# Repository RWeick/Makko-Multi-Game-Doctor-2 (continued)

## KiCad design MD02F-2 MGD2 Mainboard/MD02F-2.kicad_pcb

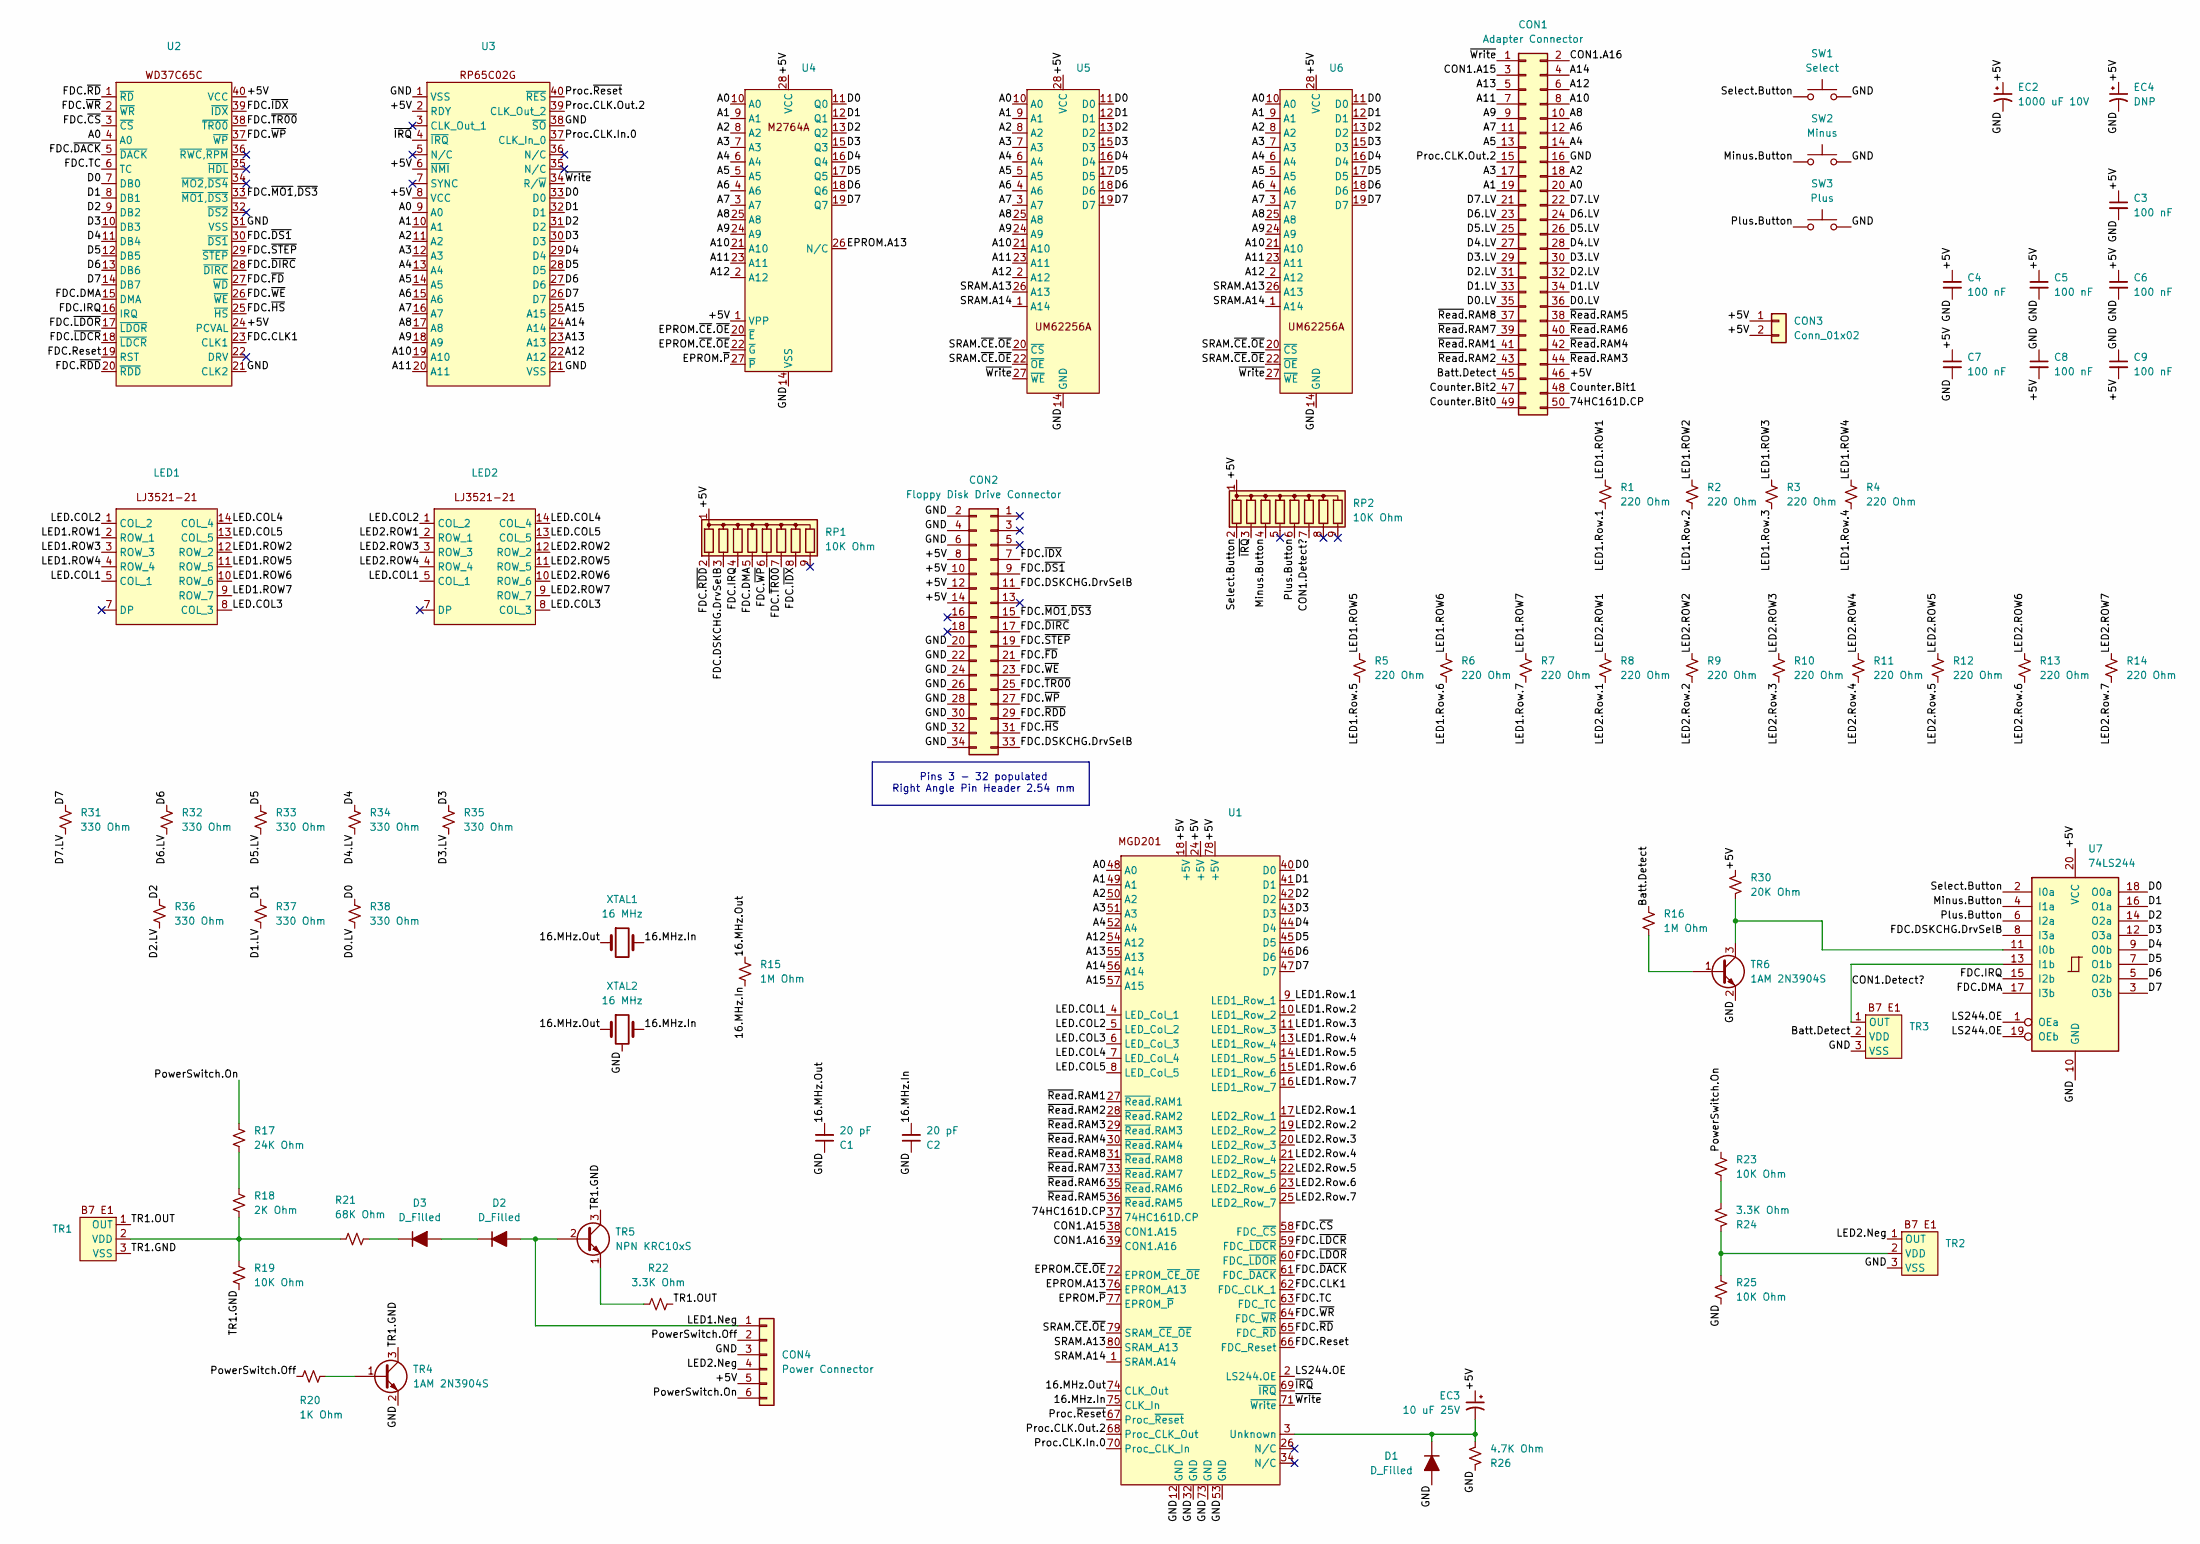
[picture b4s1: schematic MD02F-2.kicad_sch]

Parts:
C1, C2: 20 pF; C_1206_3216Metric
C3, C4, C5, C6, C7, C8, C9: 100 nF; C_1206_3216Metric
CON1: Adapter Connector; J050 Connector
CON2: Floppy Disk Drive Connector; PinHeader_2x17_P2.54mm_Horizontal
CON3: Conn_01x02; PinHeader_1x02_P2.54mm_Vertical
CON4: Power Connector; PinHeader_1x06_P2.54mm_Vertical
D1, D2, D3: D_Filled; D_1206_3216Metric
EC2: 1000 uF 10V; CP_Radial_D8.0mm_P3.50mm
EC3: 10 uF 25V; CP_Radial_D5.0mm_P2.50mm
EC4: DNP; C_1210_3225Metric_Pad1.33x2.70mm_HandSolder
LED1, LED2: DIP-14_W7.62mm
R1, R2, R3, R4, R5, R6, R7, R8, R9, R10, R11, R12, R13, R14: 220 Ohm; R_0805_2012Metric
R15, R16: 1M Ohm; R_0805_2012Metric
R17: 24K Ohm; R_0805_2012Metric
R18: 2K Ohm; R_0805_2012Metric
R19, R23, R25: 10K Ohm; R_0805_2012Metric
R20: 1K Ohm; R_0805_2012Metric
R21: 68K Ohm; R_0805_2012Metric
R22, R24: 3.3K Ohm; R_0805_2012Metric
R26: 4.7K Ohm; R_0805_2012Metric
R30: 20K Ohm; R_0805_2012Metric
R31, R32, R33, R34, R35, R36, R37, R38: 330 Ohm; R_0805_2012Metric
RP1, RP2: 10K Ohm; R_Array_SIP9
SW1: Select; Button
SW2: Minus; Button
SW3: Plus; Button
TR1, TR2, TR3: SOT-89-3
TR4, TR6: 1AM 2N3904S; SOT-23
TR5: NPN KRC10xS; SOT-23
U1: MGD201 QFP-80
U2, U3: DIP-40_W15.24mm
U4, U5: DIP-28_W15.24mm
U6: SOIC-28W_7.5x18.7mm_P1.27mm
U7: 74LS244; DIP-20_W7.62mm
XTAL1: 16 MHz; Crystal_AT310_D3.0mm_L10.0mm_Horizontal
XTAL2: 16 MHz; Crystal_HC18-U_Horizontal_1EP_style1

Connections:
/16.MHz.In: C2.2, R15.2, U1.75 (CLK_In), XTAL1.2, XTAL2.2
/16.MHz.Out: C1.2, R15.1, U1.74 (CLK_Out), XTAL1.1, XTAL2.1
/74HC161D.CP: CON1.50, U1.37 (74HC161D.CP)
/+5V: C3.1, C4.1, C5.1, C6.1, C7.1, C8.2, C9.2, CON1.46, CON2.8, CON2.10, CON2.12, CON2.14, CON3.1, CON3.2, CON4.5, EC2.1, EC3.1, EC4.1, R30.2, RP1.1 (common), RP2.1 (common), U1.18 (+5V), U1.24 (+5V), U1.78 (+5V), U2.24 (PCVAL), U2.40 (VCC), U3.2 (RDY), U3.6 (~NMI), U3.8 (VCC), U4.1 (VPP), U4.28 (VCC), U5.28 (VCC), U6.28 (VCC), U7.20 (VCC)
/A0: CON1.20, U1.48 (A0), U2.4 (A0), U3.9 (A0), U4.10 (A0), U5.10 (A0), U6.10 (A0)
/A1: CON1.19, U1.49 (A1), U3.10 (A1), U4.9 (A1), U5.9 (A1), U6.9 (A1)
/A2: CON1.18, U1.50 (A2), U3.11 (A2), U4.8 (A2), U5.8 (A2), U6.8 (A2)
/A3: CON1.17, U1.51 (A3), U3.12 (A3), U4.7 (A3), U5.7 (A3), U6.7 (A3)
/A4: CON1.14, U1.52 (A4), U3.13 (A4), U4.6 (A4), U5.6 (A4), U6.6 (A4)
/A5: CON1.13, U3.14 (A5), U4.5 (A5), U5.5 (A5), U6.5 (A5)
/A6: CON1.12, U3.15 (A6), U4.4 (A6), U5.4 (A6), U6.4 (A6)
/A7: CON1.11, U3.16 (A7), U4.3 (A7), U5.3 (A7), U6.3 (A7)
/A8: CON1.10, U3.17 (A8), U4.25 (A8), U5.25 (A8), U6.25 (A8)
/A9: CON1.9, U3.18 (A9), U4.24 (A9), U5.24 (A9), U6.24 (A9)
/A10: CON1.8, U3.19 (A10), U4.21 (A10), U5.21 (A10), U6.21 (A10)
/A11: CON1.7, U3.20 (A11), U4.23 (A11), U5.23 (A11), U6.23 (A11)
/A12: CON1.6, U1.54 (A12), U3.22 (A12), U4.2 (A12), U5.2 (A12), U6.2 (A12)
/A13: CON1.5, U1.55 (A13), U3.23 (A13)
/A14: CON1.4, U1.56 (A14), U3.24 (A14)
/A15: U1.57 (A15), U3.25 (A15)
/Batt.Detect: CON1.45, R16.1, TR3.2 (VDD)
/CON1.A15: CON1.3, U1.38 (CON1.A15)
/CON1.A16: CON1.2, U1.39 (CON1.A16)
/CON1.Detect?: RP2.7 (R6), TR3.1 (OUT), U7.13 (I1b)
/Counter.Bit0: CON1.49
/Counter.Bit1: CON1.48
/Counter.Bit2: CON1.47
/D0: R38.1, U1.40 (D0), U2.7 (DB0), U3.33 (D0), U4.11 (Q0), U5.11 (D0), U6.11 (D0), U7.18 (O0a)
/D0.LV: CON1.35, CON1.36, R38.2
/D1: R37.1, U1.41 (D1), U2.8 (DB1), U3.32 (D1), U4.12 (Q1), U5.12 (D1), U6.12 (D1), U7.16 (O1a)
/D1.LV: CON1.33, CON1.34, R37.2
/D2: R36.1, U1.42 (D2), U2.9 (DB2), U3.31 (D2), U4.13 (Q2), U5.13 (D2), U6.13 (D2), U7.14 (O2a)
/D2.LV: CON1.31, CON1.32, R36.2
/D3: R35.1, U1.43 (D3), U2.10 (DB3), U3.30 (D3), U4.15 (Q3), U5.15 (D3), U6.15 (D3), U7.12 (O3a)
/D3.LV: CON1.29, CON1.30, R35.2
/D4: R34.1, U1.44 (D4), U2.11 (DB4), U3.29 (D4), U4.16 (Q4), U5.16 (D4), U6.16 (D4), U7.9 (O0b)
/D4.LV: CON1.27, CON1.28, R34.2
/D5: R33.1, U1.45 (D5), U2.12 (DB5), U3.28 (D5), U4.17 (Q5), U5.17 (D5), U6.17 (D5), U7.7 (O1b)
/D5.LV: CON1.25, CON1.26, R33.2
/D6: R32.1, U1.46 (D6), U2.13 (DB6), U3.27 (D6), U4.18 (Q6), U5.18 (D6), U6.18 (D6), U7.5 (O2b)
/D6.LV: CON1.23, CON1.24, R32.2
/D7: R31.1, U1.47 (D7), U2.14 (DB7), U3.26 (D7), U4.19 (Q7), U5.19 (D7), U6.19 (D7), U7.3 (O3b)
/D7.LV: CON1.21, CON1.22, R31.2
/EPROM.A13: U1.76 (EPROM_A13), U4.26 (N/C)
/EPROM.~CE.~OE: U1.72 (EPROM_~CE_~OE), U4.20 (~E), U4.22 (~G)
/EPROM.~P: U1.77 (EPROM_~P), U4.27 (~P)
/FDC.CLK1: U1.62 (FDC_CLK_1), U2.23 (CLK1)
/FDC.DMA: RP1.5 (R4), U2.15 (DMA), U7.17 (I3b)
/FDC.DSKCHG.DrvSelB: CON2.11, CON2.33, RP1.3 (R2), U7.8 (I3a)
/FDC.IRQ: RP1.4 (R3), U2.16 (IRQ), U7.15 (I2b)
/FDC.Reset: U1.66 (FDC_Reset), U2.19 (RST)
/FDC.TC: U1.63 (FDC_TC), U2.6 (TC)
/FDC.~CS: U1.58 (FDC_~CS), U2.3 (~CS)
/FDC.~DACK: U1.61 (FDC_~DACK), U2.5 (~DACK)
/FDC.~DIRC: CON2.17, U2.28 (~DIRC)
/FDC.~DS1: CON2.9, U2.30 (~DS1)
/FDC.~FD: CON2.21, U2.27 (~WD)
/FDC.~HS: CON2.31, U2.25 (~HS)
/FDC.~IDX: CON2.7, RP1.8 (R7), U2.39 (~IDX)
/FDC.~LDCR: U1.59 (FDC_~LDCR), U2.18 (~LDCR)
/FDC.~LDOR: U1.60 (FDC_~LDOR), U2.17 (~LDOR)
/FDC.~MO1,~DS3: CON2.15, U2.33 (~MO1,~DS3)
/FDC.~RDD: CON2.29, RP1.2 (R1), U2.20 (~RDD)
/FDC.~RD: U1.65 (FDC_~RD), U2.1 (~RD)
/FDC.~STEP: CON2.19, U2.29 (~STEP)
/FDC.~TR00: CON2.25, RP1.7 (R6), U2.38 (~TR00)
/FDC.~WE: CON2.23, U2.26 (~WE)
/FDC.~WP: CON2.27, RP1.6 (R5), U2.37 (~WP)
/FDC.~WR: U1.64 (FDC_~WR), U2.2 (~WR)
/GND: C1.1, C2.1, C3.2, C4.2, C5.2, C6.2, C7.2, C8.1, C9.1, CON1.16, CON2.2, CON2.4, CON2.6, CON2.20, CON2.22, CON2.24, CON2.26, CON2.28, CON2.30, CON2.32, CON2.34, CON4.3, D1.2 (A), EC2.2, EC4.2, R25.2, R26.1, SW1.2, SW2.2, SW3.2, TR2.3 (VSS), TR3.3 (VSS), TR4.2 (E), TR6.2 (E), U1.12 (GND), U1.32 (GND), U1.53 (GND), U1.73 (GND), U2.21 (CLK2), U2.31 (VSS), U3.1 (VSS), U3.21 (VSS), U3.38 (~SO), U4.14 (VSS), U5.14 (GND), U6.14 (GND), U7.10 (GND), XTAL2.3
/LED1.Neg: CON4.1, D2.2 (A), TR5.2 (B)
/LED1.ROW1: LED1.2 (ROW_1), R1.1
/LED1.ROW2: LED1.12 (ROW_2), R2.1
/LED1.ROW3: LED1.3 (ROW_3), R3.1
/LED1.ROW4: LED1.4 (ROW_4), R4.1
/LED1.ROW5: LED1.11 (ROW_5), R5.1
/LED1.ROW6: LED1.10 (ROW_6), R6.1
/LED1.ROW7: LED1.9 (ROW_7), R7.1
/LED1.Row.1: R1.2, U1.9 (LED1_Row_1)
/LED1.Row.2: R2.2, U1.10 (LED1_Row_2)
/LED1.Row.3: R3.2, U1.11 (LED1_Row_3)
/LED1.Row.4: R4.2, U1.13 (LED1_Row_4)
/LED1.Row.5: R5.2, U1.14 (LED1_Row_5)
/LED1.Row.6: R6.2, U1.15 (LED1_Row_6)
/LED1.Row.7: R7.2, U1.16 (LED1_Row_7)
/LED2.Neg: CON4.4, TR2.1 (OUT)
/LED2.ROW1: LED2.2 (ROW_1), R8.1
/LED2.ROW2: LED2.12 (ROW_2), R9.1
/LED2.ROW3: LED2.3 (ROW_3), R10.1
/LED2.ROW4: LED2.4 (ROW_4), R11.1
/LED2.ROW5: LED2.11 (ROW_5), R12.1
/LED2.ROW6: LED2.10 (ROW_6), R13.1
/LED2.ROW7: LED2.9 (ROW_7), R14.1
/LED2.Row.1: R8.2, U1.17 (LED2_Row_1)
/LED2.Row.2: R9.2, U1.19 (LED2_Row_2)
/LED2.Row.3: R10.2, U1.20 (LED2_Row_3)
/LED2.Row.4: R11.2, U1.21 (LED2_Row_4)
/LED2.Row.5: R12.2, U1.22 (LED2_Row_5)
/LED2.Row.6: R13.2, U1.23 (LED2_Row_6)
/LED2.Row.7: R14.2, U1.25 (LED2_Row_7)
/LED.COL1: LED1.5 (COL_1), LED2.5 (COL_1), U1.4 (LED_Col_1)
/LED.COL2: LED1.1 (COL_2), LED2.1 (COL_2), U1.5 (LED_Col_2)
/LED.COL3: LED1.8 (COL_3), LED2.8 (COL_3), U1.6 (LED_Col_3)
/LED.COL4: LED1.14 (COL_4), LED2.14 (COL_4), U1.7 (LED_Col_4)
/LED.COL5: LED1.13 (COL_5), LED2.13 (COL_5), U1.8 (LED_Col_5)
/LS244.OE: U1.2 (LS244.OE), U7.1 (OEa), U7.19 (OEb)
/Minus.Button: RP2.4 (R3), SW2.1, U7.4 (I1a)
/Plus.Button: RP2.6 (R5), SW3.1, U7.6 (I2a)
/PowerSwitch.Off: CON4.2, R20.2
/PowerSwitch.On: CON4.6, R17.1, R23.1
/Proc.CLK.In.0: U1.70 (Proc_CLK_In), U3.37 (CLK_In_0)
/Proc.CLK.Out.2: CON1.15, U1.68 (Proc_CLK_Out), U3.39 (CLK_Out_2)
/Proc.~Reset: U1.67 (Proc_~Reset), U3.40 (~RES)
/SRAM.A13: U1.80 (SRAM_A13), U5.26 (A13), U6.26 (A13)
/SRAM.A14: U1.1 (SRAM.A14), U5.1 (A14), U6.1 (A14)
/SRAM.~CE.~OE: U1.79 (SRAM_~CE_~OE), U5.20 (~CS), U5.22 (~OE), U6.20 (~CS), U6.22 (~OE)
/Select.Button: RP2.2 (R1), SW1.1, U7.2 (I0a)
/TR1.GND: R19.2, TR1.3 (VSS), TR4.3 (C), TR5.3 (C)
/TR1.OUT: R22.2, TR1.1 (OUT)
/~IRQ: RP2.3 (R2), U1.69 (~IRQ), U3.4 (~IRQ)
/~Read.RAM1: CON1.41, U1.27 (~Read.RAM1)
/~Read.RAM2: CON1.43, U1.28 (~Read.RAM2)
/~Read.RAM3: CON1.44, U1.29 (~Read.RAM3)
/~Read.RAM4: CON1.42, U1.30 (~Read.RAM4)
/~Read.RAM5: CON1.38, U1.36 (~Read.RAM5)
/~Read.RAM6: CON1.40, U1.35 (~Read.RAM6)
/~Read.RAM7: CON1.39, U1.33 (~Read.RAM7)
/~Read.RAM8: CON1.37, U1.31 (~Read.RAM8)
/~Write: CON1.1, U1.71 (~Write), U3.34 (R/~W), U5.27 (~WE), U6.27 (~WE)
unnamed: D1.1 (K), EC3.2, R26.2, U1.3 (Unknown)
unnamed: D2.1 (K), D3.2 (A)
unnamed: D3.1 (K), R21.1
unnamed: R17.2, R18.1
unnamed: R23.2, R24.2
unnamed: R18.2, R19.1, R21.2, TR1.2 (VDD)
unnamed: R24.1, R25.1, TR2.2 (VDD)
unnamed: R20.1, TR4.1 (B)
unnamed: R22.1, TR5.1 (E)
unnamed: R16.2, TR6.1 (B)
unnamed: R30.1, TR6.3 (C), U7.11 (I0b)

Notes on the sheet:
Pins 3 - 32 populated Right Angle Pin Header 2.54 mm

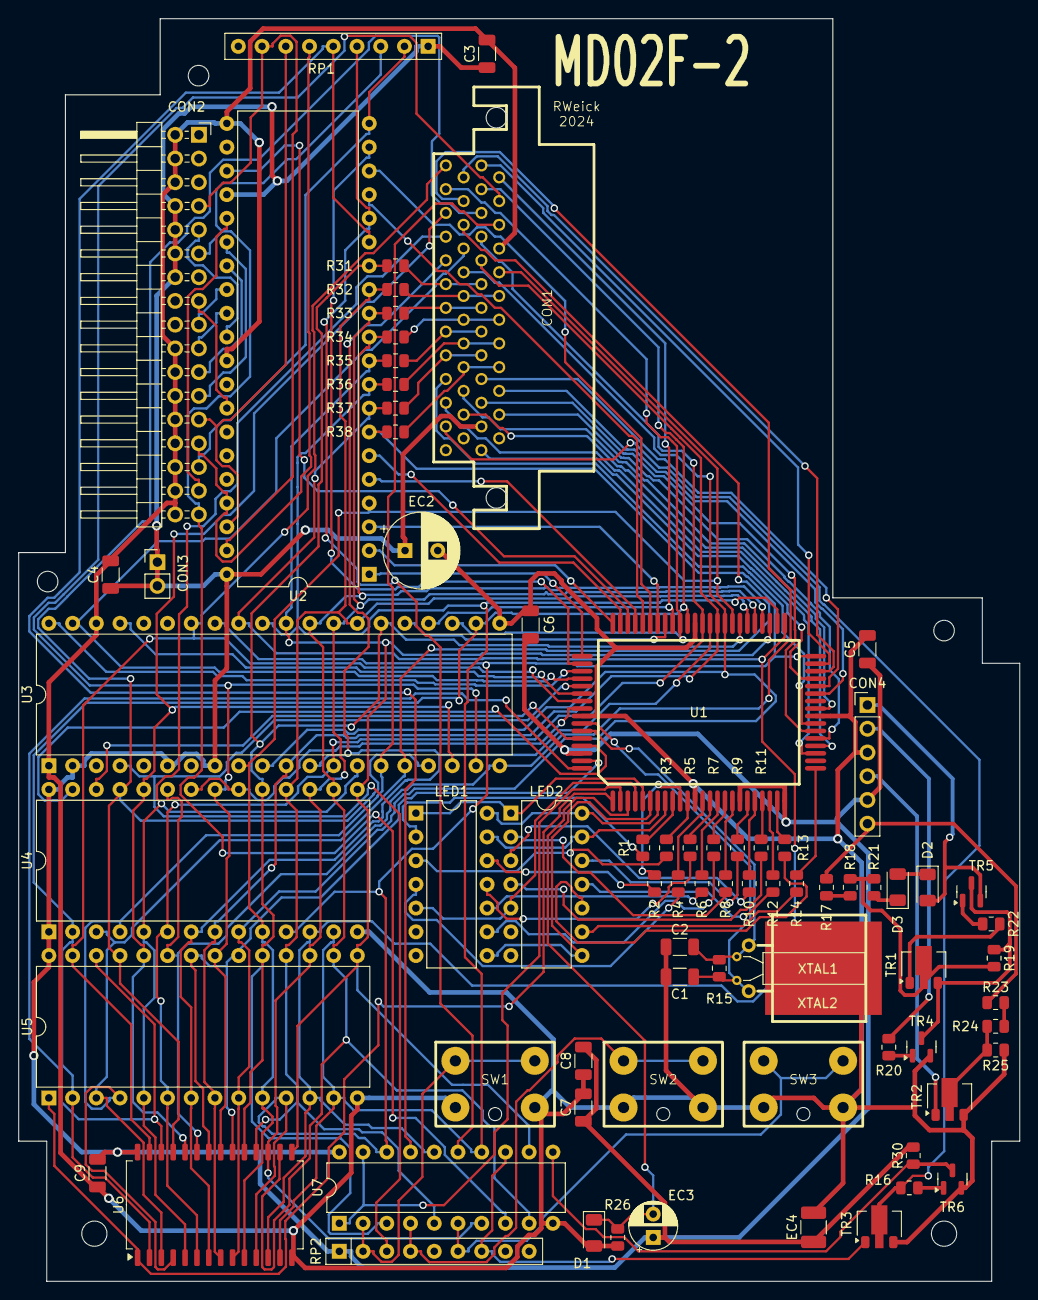
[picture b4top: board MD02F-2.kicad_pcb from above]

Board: 2 copper layers, 107.1 x 135.2 mm, 76 parts (0 on the bottom side), 137 nets.

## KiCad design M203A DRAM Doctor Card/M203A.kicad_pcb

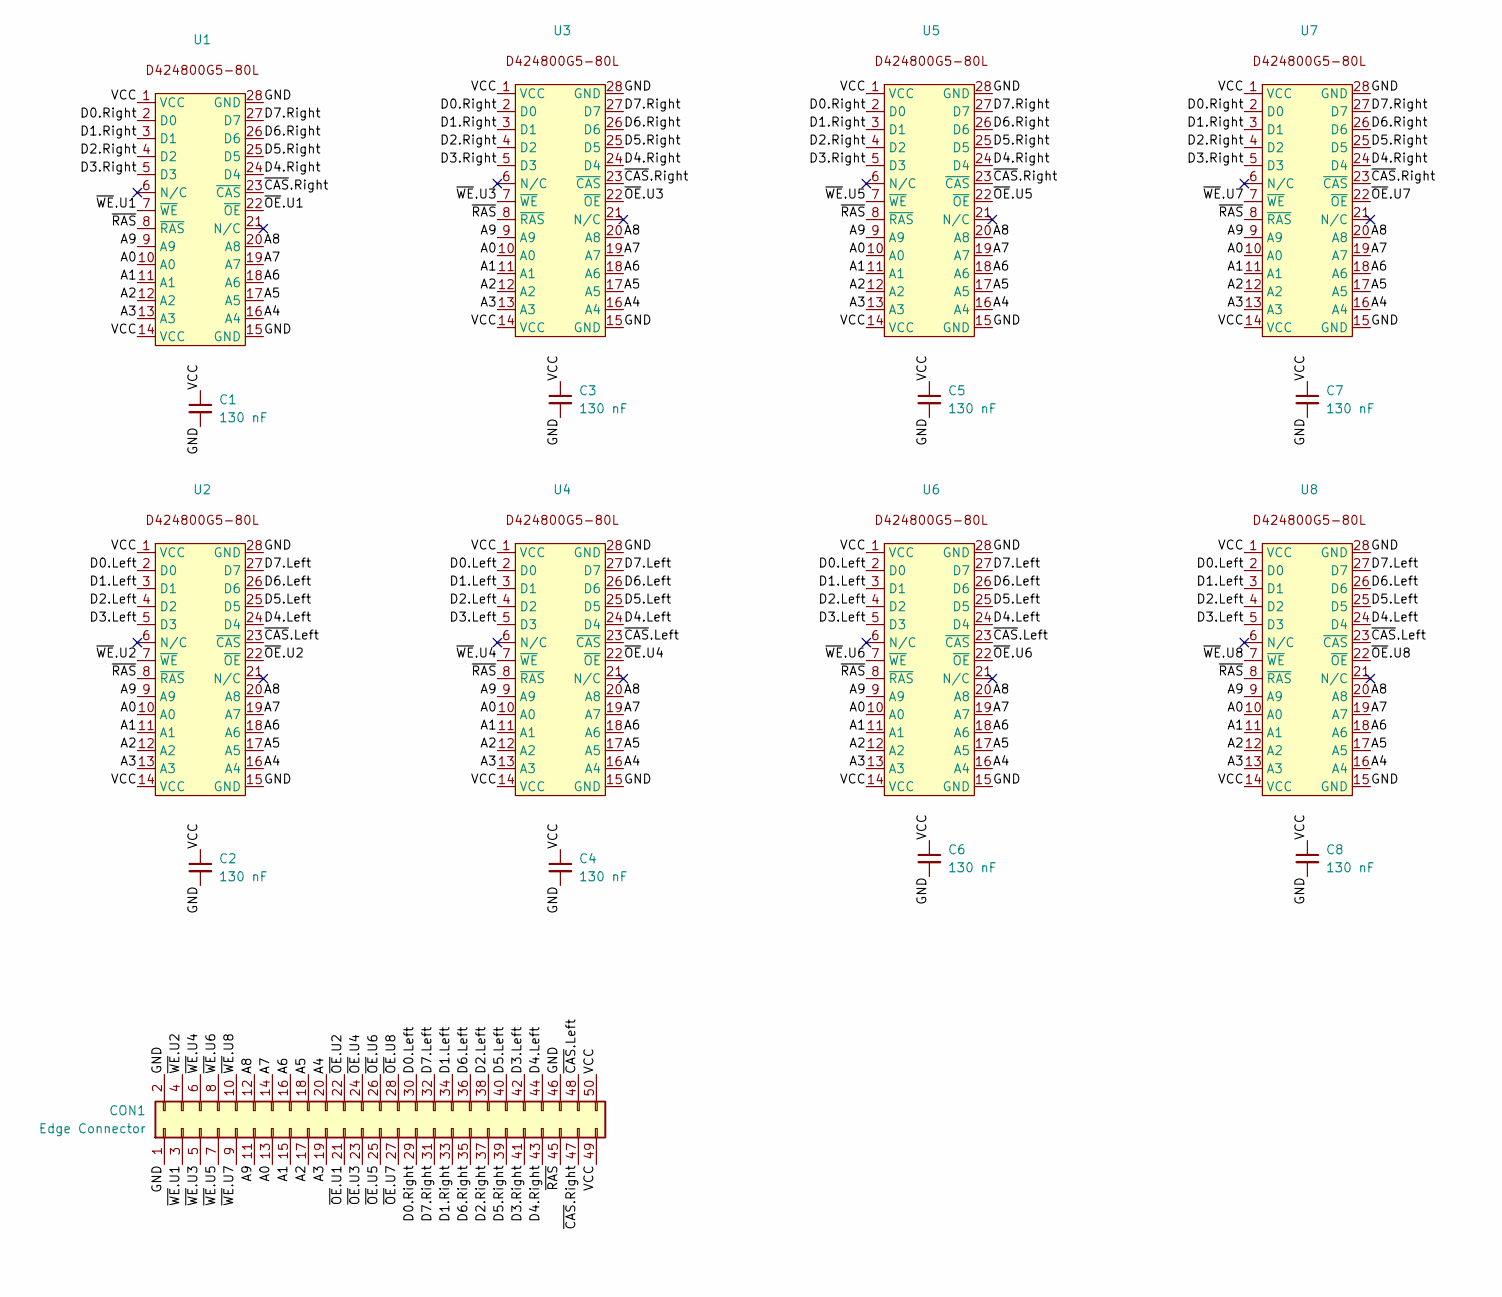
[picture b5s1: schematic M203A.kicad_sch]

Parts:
C1, C2, C3, C4, C5, C6, C7, C8: 130 nF; Capacitor
CON1: Edge Connector
U1, U2, U3, U4, U5, U6, U7, U8: SOIC-28

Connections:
/A0: CON1.13, U1.10 (A0), U2.10 (A0), U3.10 (A0), U4.10 (A0), U5.10 (A0), U6.10 (A0), U7.10 (A0), U8.10 (A0)
/A1: CON1.15, U1.11 (A1), U2.11 (A1), U3.11 (A1), U4.11 (A1), U5.11 (A1), U6.11 (A1), U7.11 (A1), U8.11 (A1)
/A2: CON1.17, U1.12 (A2), U2.12 (A2), U3.12 (A2), U4.12 (A2), U5.12 (A2), U6.12 (A2), U7.12 (A2), U8.12 (A2)
/A3: CON1.19, U1.13 (A3), U2.13 (A3), U3.13 (A3), U4.13 (A3), U5.13 (A3), U6.13 (A3), U7.13 (A3), U8.13 (A3)
/A4: CON1.20, U1.16 (A4), U2.16 (A4), U3.16 (A4), U4.16 (A4), U5.16 (A4), U6.16 (A4), U7.16 (A4), U8.16 (A4)
/A5: CON1.18, U1.17 (A5), U2.17 (A5), U3.17 (A5), U4.17 (A5), U5.17 (A5), U6.17 (A5), U7.17 (A5), U8.17 (A5)
/A6: CON1.16, U1.18 (A6), U2.18 (A6), U3.18 (A6), U4.18 (A6), U5.18 (A6), U6.18 (A6), U7.18 (A6), U8.18 (A6)
/A7: CON1.14, U1.19 (A7), U2.19 (A7), U3.19 (A7), U4.19 (A7), U5.19 (A7), U6.19 (A7), U7.19 (A7), U8.19 (A7)
/A8: CON1.12, U1.20 (A8), U2.20 (A8), U3.20 (A8), U4.20 (A8), U5.20 (A8), U6.20 (A8), U7.20 (A8), U8.20 (A8)
/A9: CON1.11, U1.9 (A9), U2.9 (A9), U3.9 (A9), U4.9 (A9), U5.9 (A9), U6.9 (A9), U7.9 (A9), U8.9 (A9)
/D0.Left: CON1.30, U2.2 (D0), U4.2 (D0), U6.2 (D0), U8.2 (D0)
/D0.Right: CON1.29, U1.2 (D0), U3.2 (D0), U5.2 (D0), U7.2 (D0)
/D1.Left: CON1.34, U2.3 (D1), U4.3 (D1), U6.3 (D1), U8.3 (D1)
/D1.Right: CON1.33, U1.3 (D1), U3.3 (D1), U5.3 (D1), U7.3 (D1)
/D2.Left: CON1.38, U2.4 (D2), U4.4 (D2), U6.4 (D2), U8.4 (D2)
/D2.Right: CON1.37, U1.4 (D2), U3.4 (D2), U5.4 (D2), U7.4 (D2)
/D3.Left: CON1.42, U2.5 (D3), U4.5 (D3), U6.5 (D3), U8.5 (D3)
/D3.Right: CON1.41, U1.5 (D3), U3.5 (D3), U5.5 (D3), U7.5 (D3)
/D4.Left: CON1.44, U2.24 (D4), U4.24 (D4), U6.24 (D4), U8.24 (D4)
/D4.Right: CON1.43, U1.24 (D4), U3.24 (D4), U5.24 (D4), U7.24 (D4)
/D5.Left: CON1.40, U2.25 (D5), U4.25 (D5), U6.25 (D5), U8.25 (D5)
/D5.Right: CON1.39, U1.25 (D5), U3.25 (D5), U5.25 (D5), U7.25 (D5)
/D6.Left: CON1.36, U2.26 (D6), U4.26 (D6), U6.26 (D6), U8.26 (D6)
/D6.Right: CON1.35, U1.26 (D6), U3.26 (D6), U5.26 (D6), U7.26 (D6)
/D7.Left: CON1.32, U2.27 (D7), U4.27 (D7), U6.27 (D7), U8.27 (D7)
/D7.Right: CON1.31, U1.27 (D7), U3.27 (D7), U5.27 (D7), U7.27 (D7)
/GND: C1.2, C2.2, C3.2, C4.2, C5.2, C6.2, C7.2, C8.2, CON1.1, CON1.2, CON1.46, U1.15 (GND), U1.28 (GND), U2.15 (GND), U2.28 (GND), U3.15 (GND), U3.28 (GND), U4.15 (GND), U4.28 (GND), U5.15 (GND), U5.28 (GND), U6.15 (GND), U6.28 (GND), U7.15 (GND), U7.28 (GND), U8.15 (GND), U8.28 (GND)
/VCC: C1.1, C2.1, C3.1, C4.1, C5.1, C6.1, C7.1, C8.1, CON1.49, CON1.50, U1.1 (VCC), U1.14 (VCC), U2.1 (VCC), U2.14 (VCC), U3.1 (VCC), U3.14 (VCC), U4.1 (VCC), U4.14 (VCC), U5.1 (VCC), U5.14 (VCC), U6.1 (VCC), U6.14 (VCC), U7.1 (VCC), U7.14 (VCC), U8.1 (VCC), U8.14 (VCC)
/~CAS.Left: CON1.48, U2.23 (~CAS), U4.23 (~CAS), U6.23 (~CAS), U8.23 (~CAS)
/~CAS.Right: CON1.47, U1.23 (~CAS), U3.23 (~CAS), U5.23 (~CAS), U7.23 (~CAS)
/~OE.U1: CON1.21, U1.22 (~OE)
/~OE.U2: CON1.22, U2.22 (~OE)
/~OE.U3: CON1.23, U3.22 (~OE)
/~OE.U4: CON1.24, U4.22 (~OE)
/~OE.U5: CON1.25, U5.22 (~OE)
/~OE.U6: CON1.26, U6.22 (~OE)
/~OE.U7: CON1.27, U7.22 (~OE)
/~OE.U8: CON1.28, U8.22 (~OE)
/~RAS: CON1.45, U1.8 (~RAS), U2.8 (~RAS), U3.8 (~RAS), U4.8 (~RAS), U5.8 (~RAS), U6.8 (~RAS), U7.8 (~RAS), U8.8 (~RAS)
/~WE.U1: CON1.3, U1.7 (~WE)
/~WE.U2: CON1.4, U2.7 (~WE)
/~WE.U3: CON1.5, U3.7 (~WE)
/~WE.U4: CON1.6, U4.7 (~WE)
/~WE.U5: CON1.7, U5.7 (~WE)
/~WE.U6: CON1.8, U6.7 (~WE)
/~WE.U7: CON1.9, U7.7 (~WE)
/~WE.U8: CON1.10, U8.7 (~WE)

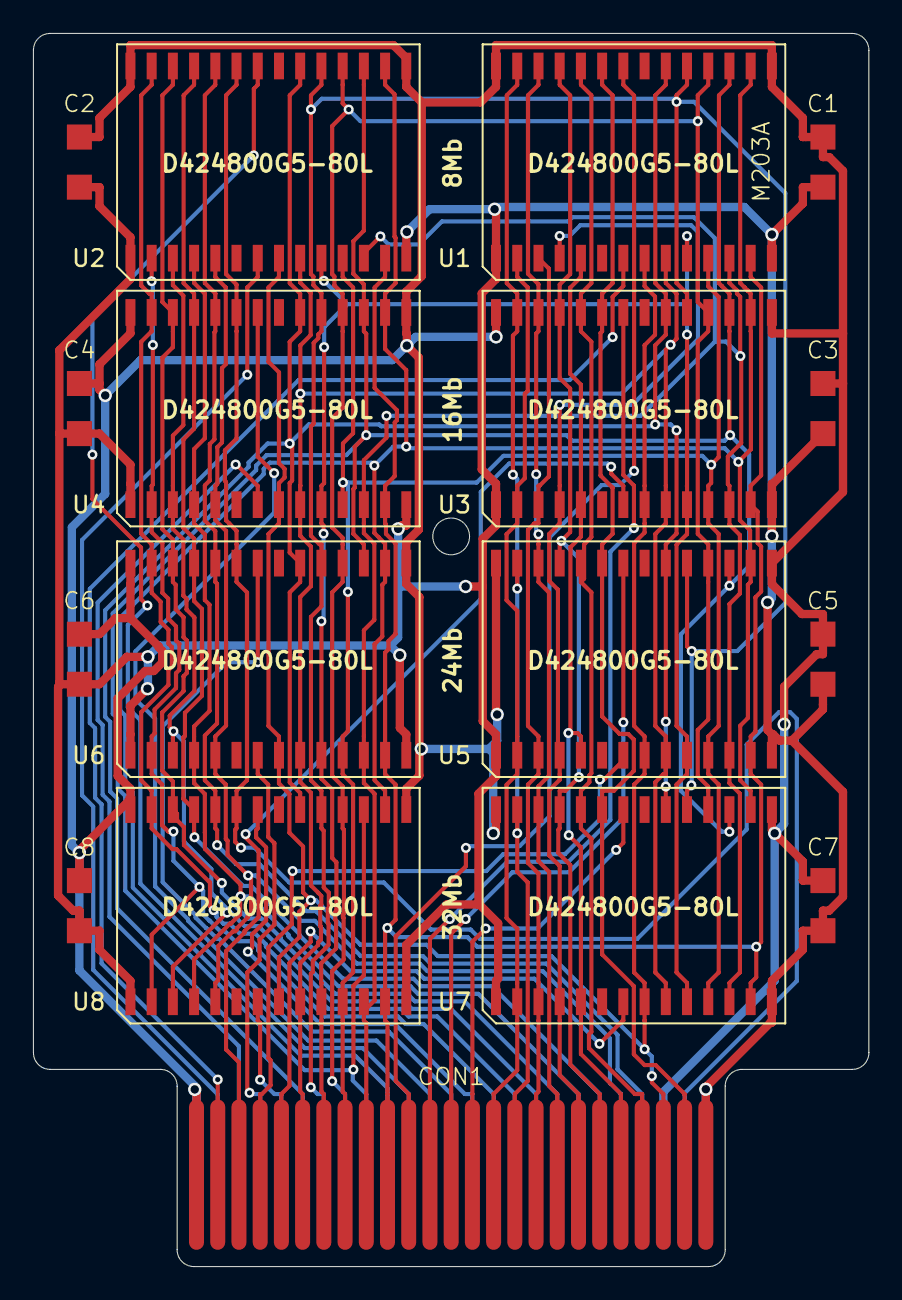
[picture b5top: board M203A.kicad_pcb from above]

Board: 2 copper layers, 50.0 x 73.8 mm, 17 parts (0 on the bottom side), 47 nets.

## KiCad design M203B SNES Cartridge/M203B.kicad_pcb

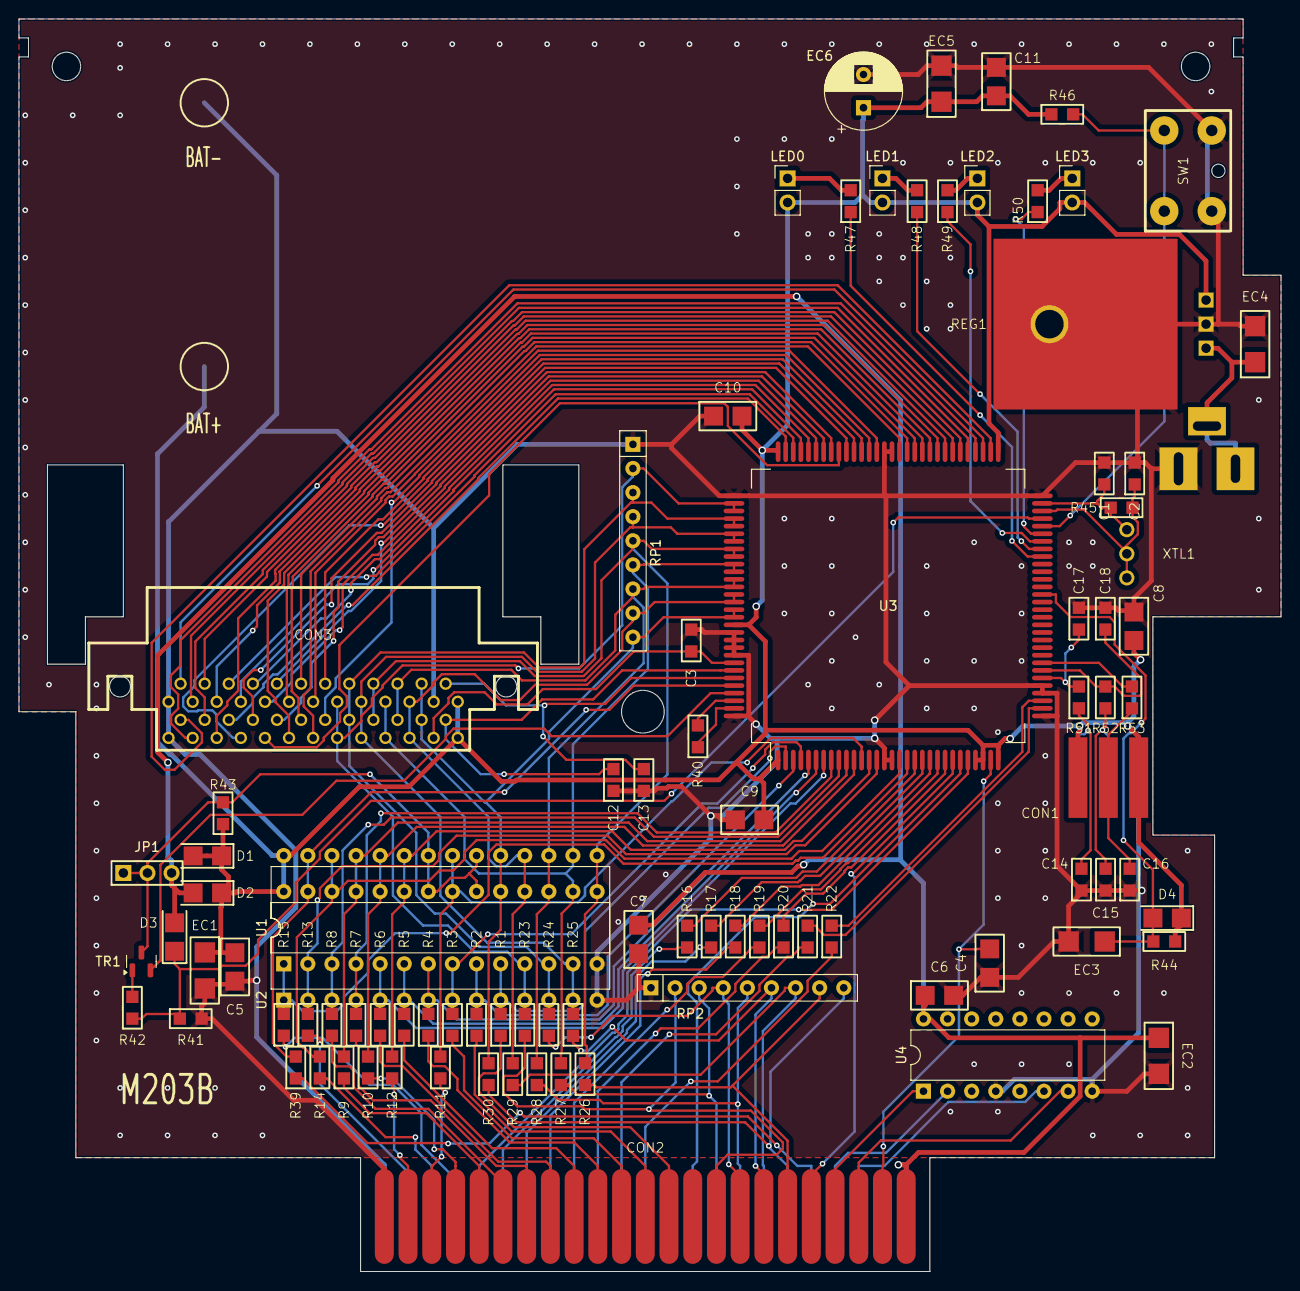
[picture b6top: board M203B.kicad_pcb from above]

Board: 2 copper layers, 133.0 x 132.0 mm, 93 parts (0 on the bottom side), 127 nets.

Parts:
BT1: Battery_Cell; Battery
C1, C2: 20 pF; Resistor
C3, C12, C13, C16: DNP; Resistor
C4: DNP; Capacitor
C5, C6, C7, C8, C9, C10, C11: 200 nF; Capacitor
C14, C15: 190 pF; Resistor
C17, C18: 100 pF; Resistor
CON1: RJ12 Board Connector; RJ-12 Pads
CON2: Edge Connector
CON3: RAM Board Slot; J050 Connector
D1, D2: DNP; Diode
D3: 330 Ohm Resistor; Diode
D4: Populated; Diode
EC1, EC5: DNP; ECap
EC2, EC3: 106 6.3V; ECap
EC4: 200 nF SMD; ECap
EC6: 220 uF 16V; CP_Radial_D8.0mm_P3.50mm
J1: Barrel_Jack_Switch; DC Jack
JP1: DNP; PinHeader_1x03_P2.54mm_Vertical
LED0, LED1, LED2, LED3: LED; PinHeader_1x02_P2.54mm_Vertical
R1, R2, R3, R4, R5, R6, R7, R8, R9, R10, R11, R12, R13, R14, R15, R16, R17, R18, R19, R20, R21, R22, R23, R24, R25, R26, R27, R28, R29, R30, R39, R40, R41, R47, R48, R49, R50, R51, R52, R53: 330 Ohm; Resistor
R42: 1K Ohm; Resistor
R43: Oh Boy; Resistor
R44, R46: 10K Ohm; Resistor
R45: DNP; Resistor
REG1: VREG
RP1, RP2: DNP; R_Array_SIP9
SW1: SW_Push; Button
TR1: 2N3904S; SOT-23
U1: DIP-28_W7.62mm
U2: DIP-28_W15.24mm
U3: MGD203
U4: DIP-16_W7.62mm
XTL1: 16 MHz; Crystal

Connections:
/9V.In: EC4.1, J1.2, REG1.1 (VIN)
/+5V: BT1.1 (+), C5.2, C8.1, C9.2, C10.2, C11.1, CON1.1, CON1.3, CON3.49, CON3.50, D1.1 (K), D1.2 (A), D2.1 (K), D4.1 (K), EC1.1, EC5.1, EC6.1, LED0.2 (A), LED1.2 (A), LED2.2 (A), LED3.2 (A), R43.1, R44.2, R46.1, REG1.3 (VOUT), U1.28 (VCC), U2.28 (VCC), U3.1 (+5V), U3.27 (+5V), U3.28 (+5V), U3.30 (+5V), U3.61 (+5V), U3.90 (+5V), U3.108 (+5V)
/A0: R1.2, U1.10 (A0), U2.10 (A0), U3.2 (A0)
/A0.RAM: CON3.13, U3.80 (A0.RAM)
/A0.Sys: CON2.17 (A0), R1.1
/A1: R2.2, U1.9 (A1), U2.9 (A1), U3.3 (A1)
/A1.RAM: CON3.15, U3.81 (A1.RAM)
/A1.Sys: CON2.16 (A1), R2.1
/A2: R3.2, U1.8 (A2), U2.8 (A2), U3.4 (A2)
/A2.RAM: CON3.17, U3.82 (A2.RAM)
/A2.Sys: CON2.15 (A2), R3.1
/A3: R4.2, U1.7 (A3), U2.7 (A3), U3.5 (A3)
/A3.RAM: CON3.19, U3.83 (A3.RAM)
/A3.Sys: CON2.14 (A3), R4.1
/A4: R5.2, U1.6 (A4), U2.6 (A4), U3.6 (A4)
/A4.RAM: CON3.20, U3.84 (A4.RAM)
/A4.Sys: CON2.13 (A4), R5.1
/A5: R6.2, U1.5 (A5), U2.5 (A5), U3.7 (A5)
/A5.RAM: CON3.18, U3.85 (A5.RAM)
/A5.Sys: CON2.12 (A5), R6.1
/A6: R7.2, U1.4 (A6), U2.4 (A6), U3.8 (A6)
/A6.RAM: CON3.16, U3.86 (A6.RAM)
/A6.Sys: CON2.11 (A6), R7.1
/A7: R8.2, U1.3 (A7), U2.3 (A7), U3.9 (A7)
/A7.RAM: CON3.14, U3.87 (A7.RAM)
/A7.Sys: CON2.10 (A7), R8.1
/A8: R9.2, U1.25 (A8), U2.25 (A8), U3.10 (A8)
/A8.RAM: CON3.12, U3.88 (A8.RAM)
/A8.Sys: CON2.9 (A8), R9.1
/A9: R10.2, U1.24 (A9), U2.24 (A9), U3.11 (A9)
/A9.RAM: CON3.11, U3.89 (A9.RAM)
/A9.Sys: CON2.8 (A9), R10.1
/A10: R11.2, U1.21 (A10), U2.21 (A10), U3.12 (A10)
/A10.Sys: CON2.7 (A10), R11.1
/A11: R12.2, U1.23 (A11), U2.23 (A11), U3.13 (A11)
/A11.Sys: CON2.6 (A11), R12.1
/A12: R13.2, U1.2 (A12), U2.2 (A12), U3.14 (A12)
/A12.Sys: CON2.37 (A12), R13.1
/A13: R14.2, U1.26 (A13), U2.26 (A13), U3.17 (A13)
/A13.Sys: CON2.38 (A13), R14.1
/A14: R15.2, U1.1 (A14), U2.1 (A14), U3.18 (A14)
/A14.Sys: CON2.39 (A14), R15.1
/A15.Sys: CON2.40 (A15), U3.26 (A15.Sys)
/BA0: R16.2, U3.19 (BA0)
/BA0.Sys: CON2.41 (BA0), R16.1
/BA1: R17.2, U3.20 (BA1)
/BA1.Sys: CON2.42 (BA1), R17.1
/BA2: R18.2, U3.21 (BA2)
/BA2.Sys: CON2.43 (BA2), R18.1
/BA3: R19.2, U3.22 (BA3)
/BA3.Sys: CON2.44 (BA3), R19.1
/BA4: R20.2, U3.23 (BA4)
/BA4.Sys: CON2.45 (BA4), R20.1
/BA5: R21.2, U3.32 (BA5)
/BA5.Sys: CON2.46 (BA5), R21.1
/BA6: R22.2, U3.33 (BA6)
/BA6.Sys: CON2.47 (BA6), R22.1
/Button: R46.2, SW1.1, U3.56 (Button)
/CIC.In.P6: CON2.56 (CIC_In_P6), U4.6
/CIC.In.P7: CON2.25 (CIC_In_P7), U4.7
/CIC.Out.P1.Sys: CON2.24 (CIC_Out_P1), U4.1
/CIC.Out.P2.Sys: CON2.55 (CIC_Out_P2), U4.2
/CLK.In: C1.1, R45.1, U3.59 (CLK_In), XTL1.1
/CLK.Out: C2.1, R45.2, U3.58 (CLK_Out), XTL1.2, XTL1.3
/D0: CON3.29, CON3.30, R23.2, RP1.2 (R1), U1.11 (D0), U2.11 (D0), U3.92 (D0), U3.93 (D0)
/D0.Sys: CON2.19 (D0), R23.1, RP2.2 (R1)
/D1: CON3.31, CON3.32, R24.2, RP1.3 (R2), U1.12 (D1), U2.12 (D1), U3.94 (D1), U3.95 (D1)
/D1.Sys: CON2.20 (D1), R24.1, RP2.4 (R3)
/D2: CON3.33, CON3.34, R25.2, RP1.4 (R3), U1.13 (D2), U2.13 (D2), U3.96 (D2), U3.97 (D2)
/D2.Sys: CON2.21 (D2), R25.1, RP2.6 (R5)
/D3: CON3.35, CON3.36, R26.2, RP1.5 (R4), U1.15 (D3), U2.15 (D3), U3.98 (D3), U3.99 (D3)
/D3.Sys: CON2.22 (D3), R26.1, RP2.8 (R7)
/D4: CON3.37, CON3.38, R27.2, RP1.6 (R5), U1.16 (D4), U2.16 (D4), U3.100 (D4), U3.101 (D4)
/D4.Sys: CON2.50 (D4), R27.1, RP2.3 (R2)
/D5: CON3.39, CON3.40, R28.2, RP1.7 (R6), U1.17 (D5), U2.17 (D5), U3.102 (D5), U3.103 (D5)
/D5.Sys: CON2.51 (D5), R28.1, RP2.5 (R4)
/D6: CON3.41, CON3.42, R29.2, RP1.8 (R7), U1.18 (D6), U2.18 (D6), U3.104 (D6), U3.105 (D6)
/D6.Sys: CON2.52 (D6), R29.1, RP2.7 (R6)
/D7: CON3.43, CON3.44, R30.2, RP1.9 (R8), U1.19 (D7), U2.19 (D7), U3.106 (D7), U3.107 (D7)
/D7.Sys: CON2.53 (D7), R30.1, RP2.9 (R8)
/GND: BT1.2 (-), C1.2, C2.2, C3.2, C4.1, C5.1, C6.2, C7.1, C8.2, C9.1, C10.1, C11.2, C12.1, C13.1, C14.1, C15.1, C16.1, C17.2, C18.2, CON1.4, CON2.5 (GND), CON2.36 (GND), CON3.1, CON3.2, CON3.46, EC1.2, EC2.2, EC3.2, EC4.2, EC5.2, EC6.2, J1.1, R41.2, REG1.2 (GND), RP1.1 (common), RP2.1 (common), SW1.2, U1.14 (GND), U2.14 (GND), U3.15 (GND), U3.16 (GND), U3.31 (GND), U3.34 (GND), U3.35 (GND), U3.60 (GND), U3.75 (GND), U3.76 (GND), U3.91 (GND), U3.109 (GND), U3.110 (GND), U3.111 (GND), U3.112 (GND), U3.120 (GND), U4.4, U4.8
/LED0: R47.1, U3.52 (LED_0)
/LED1: R48.1, U3.53 (LED_1)
/LED2: R49.1, U3.54 (LED_2)
/LED3: R50.1, U3.55 (LED_3)
/P36: C17.1, R51.2, U3.36 (RJ12_Pad_6)
/P37: C18.1, R52.2, U3.37 (RJ12_Pad_5)
/P38: R53.2, U3.38 (RJ12_Pad_2)
/Pwr.Good: D4.2 (A), EC3.1, R44.1, U3.47 (Pwr_Good)
/SRAM.~CE.~OE: JP1.1, JP1.2, R43.2, TR1.3 (C), U1.20 (~CE), U1.22 (~OE), U2.20 (~CE), U2.22 (~OE)
/SRAM.~EN: TR1.2 (E), U3.117 (SRAM.~EN)
/Sys.Pwr.Detect: D3.1 (K), R41.1, R42.1, U3.57 (SNES_Pwr_Detect)
/VCC.Sys: C6.1, C7.2, CON2.27 (VCC), CON2.58 (VCC), D2.2 (A), D3.2 (A), EC2.1, JP1.3, U4.16
/~CART: CON2.49 (/CART), U3.25 (~CART)
/~CAS.Left: C13.2, CON3.48, U3.115 (~CAS.Left)
/~CAS.Right: C12.2, CON3.47, U3.114 (~CAS.Right)
/~OE.U1: CON3.21, U3.70 (~OE.RAM1)
/~OE.U2: CON3.22, U3.71 (~OE.RAM2)
/~OE.U3: CON3.23, U3.72 (~OE.RAM3)
/~OE.U4: CON3.24, U3.73 (~OE.RAM4)
/~OE.U5: CON3.25, U3.74 (~OE.RAM5)
/~OE.U6: CON3.26, U3.77 (~OE.RAM6)
/~OE.U7: CON3.27, U3.78 (~OE.RAM7)
/~OE.U8: CON3.28, U3.79 (~OE.RAM8)
/~RAS: C3.1, CON3.45, U3.113 (~RAS)
/~Read.Sys: CON2.23 (/Read), U3.24 (~Read.Sys)
/~Reset: C4.2, CON2.26 (/RESET), U3.29 (~Reset)
/~WE.U1: CON3.3, U3.62 (~WE.RAM1)
/~WE.U2: CON3.4, U3.63 (~WE.RAM2)
/~WE.U3: CON3.5, U3.64 (~WE.RAM3)
/~WE.U4: CON3.6, U3.65 (~WE.RAM4)
/~WE.U5: CON3.7, U3.66 (~WE.RAM5)
/~WE.U6: CON3.8, U3.67 (~WE.RAM6)
/~WE.U7: CON3.9, U3.68 (~WE.RAM7)
/~WE.U8: CON3.10, U3.69 (~WE.RAM8)
/~Write: R39.2, U1.27 (~WE), U2.27 (~WE), U3.116 (~Write)
/~Write.Sys: CON2.54 (/Write), R39.1
unnamed: C16.2, CON1.2, R53.1
unnamed: C15.2, CON1.5, R52.1
unnamed: C14.2, CON1.6, R51.1
unnamed: LED0.1 (K), R47.2
unnamed: LED1.1 (K), R48.2
unnamed: LED2.1 (K), R49.2
unnamed: LED3.1 (K), R50.2
unnamed: R40.1, U3.119 (330_Ohm_Res)
unnamed: R40.2, U3.118 (330_Ohm_Res)
unnamed: R42.2, TR1.1 (B)
